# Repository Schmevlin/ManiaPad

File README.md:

# ManiaPad
4 button macro pad for use in rhythm games, primarily for osu!/osu!Mania, includes physical CAD and pcb design

### Parts List
* pcb based on the one in this repo
* raspberry pi pico
* 0.91" I2C SSD 1306 OLED Module
* 1x4 pin header
* 4 individual WS2812B leds
* (optional) 4 100nF 1206 SMD capacitors
* 4 kailh hotswap sockets
* 4 cherry mx style mechanical keyboard switches
* 2 6mm x 6mm x 4.3mm tactile switch (push button)
* 10 M3 x 16mm machine screws
* 10 M3 nuts
* 3D Printed Parts
  * 4 plate spacer
  * 2 key block
  * 10 button spacer
  * 1 bottom
  * 6 short spacer
  * 1 middle plate
  * 2 button extender

### Button modes/layout
Button modes and layouts are in the code as the "modes" variable, with a tuples of (function name, string name). The functions define what buttons are pressed and what behaviour is associated with each mode. To swap modes hold the top left button then press the top right button.

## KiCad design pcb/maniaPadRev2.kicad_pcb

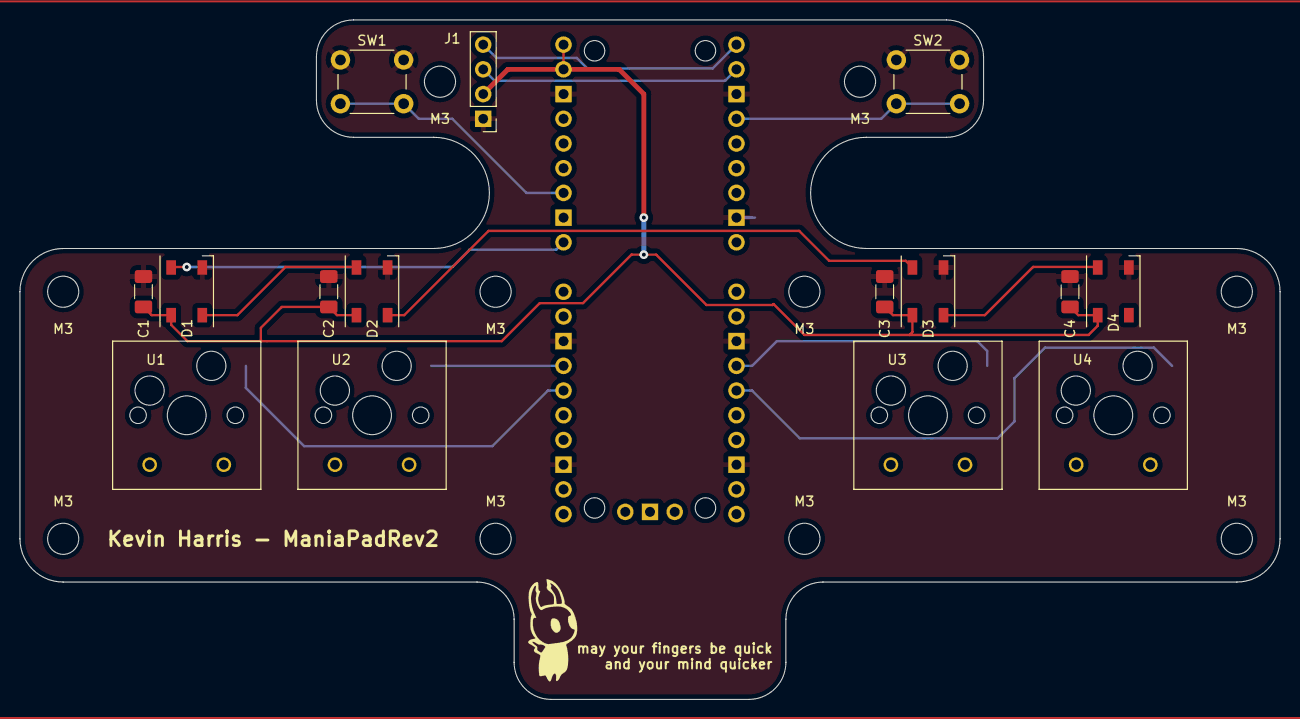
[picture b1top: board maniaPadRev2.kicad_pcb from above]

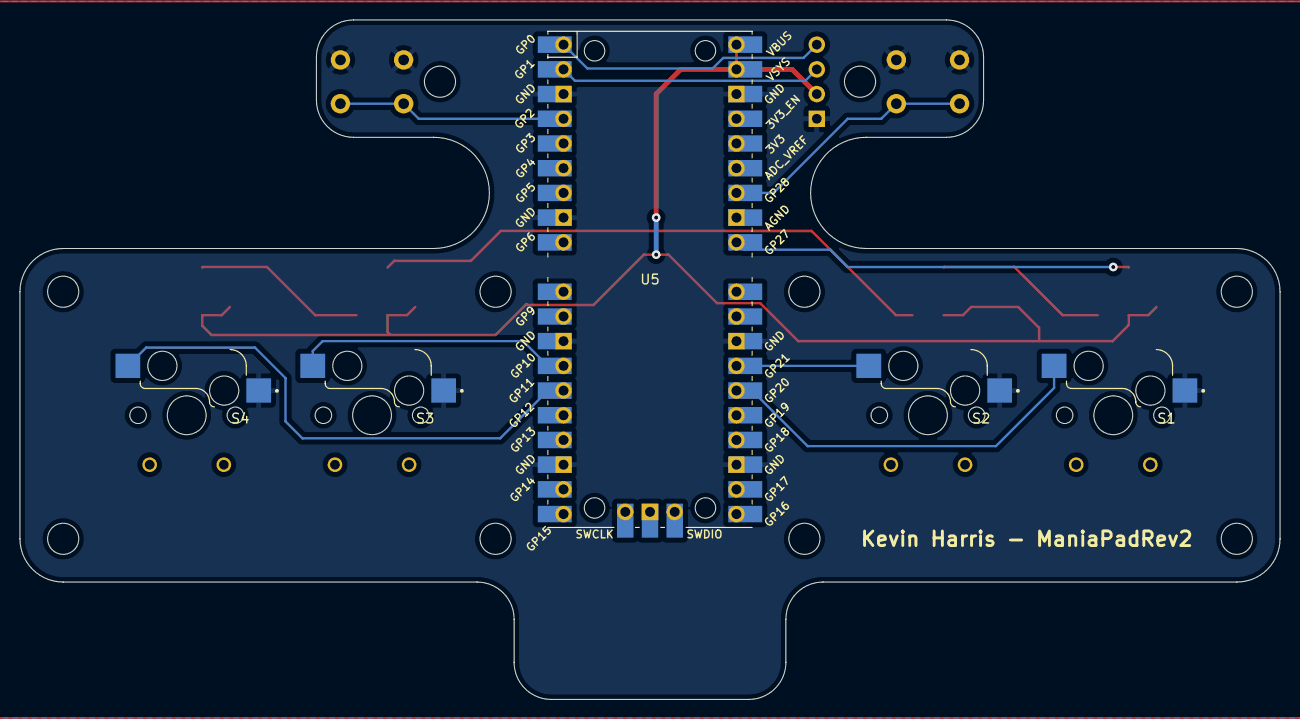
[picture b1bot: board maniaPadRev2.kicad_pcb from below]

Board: 2 copper layers, 129.5 x 69.8 mm, 30 parts (5 on the bottom side), 14 nets.

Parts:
C1, C2, C3, C4: 100nF; C_1206_3216Metric_Pad1.33x1.80mm_HandSolder
D1, D2, D3, D4: WS2812B; LED_WS2812B_PLCC4_5.0x5.0mm_P3.2mm
J1: Conn_01x04; PinHeader_1x04_P2.54mm_Vertical
M3, M3#2, M3#3, M3#4, M3#5, M3#6, M3#7, M3#8, M3#9, M3#10: MountingHole_3.2mm_M3_ISO7380
S1, S2, S3, S4: PG151101S11; SW_PG151101S11
SW1, SW2: SW_Push; SW_PUSH_6mm
U1, U2, U3, U4: MX1A-11NN; CHERRY_MX1A-11NN_SWITCH
U5: SC0915; RPi_Pico_SMD_TH

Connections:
+5V: C1.2, C2.2, C3.2, C4.2, D1.1 (VDD), D2.1 (VDD), D3.1 (VDD), D4.1 (VDD), J1.2, U5.39 (VSYS), U5.40 (VBUS)
GND: C1.1, C2.1, C3.1, C4.1, D1.3 (VSS), D2.3 (VSS), D3.3 (VSS), D4.3 (VSS), J1.1, S1.1, S2.1, S3.1, S4.1, SW1.1, SW2.1, U5.3 (GND), U5.8 (GND), U5.13 (GND), U5.18 (GND), U5.23 (GND), U5.28 (GND), U5.38 (GND)
unnamed: D1.2 (DOUT), D2.4 (DIN)
unnamed: D1.4 (DIN), U5.32 (GP27)
unnamed: D2.2 (DOUT), D3.4 (DIN)
unnamed: D3.2 (DOUT), D4.4 (DIN)
unnamed: J1.3, U5.2 (GP1)
unnamed: J1.4, U5.1 (GP0)
unnamed: S1.2, U5.26 (GP20)
unnamed: S2.2, U5.27 (GP21)
unnamed: S3.2, U5.14 (GP10)
unnamed: S4.2, U5.15 (GP11)
unnamed: SW1.2, U5.34 (GP28)
unnamed: SW2.2, U5.4 (GP2)

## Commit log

2023-01-18 Update README.md
    readme update
2023-01-20 readme upd8
2023-01-20 undo ;-;
2023-01-23 pictures
